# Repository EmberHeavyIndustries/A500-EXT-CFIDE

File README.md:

**A500-EXT-CFIDE** is an external IDE + Fast Memory Expansion for Amiga 500. 

It is basically a modified clone of Matthias Heinrich's CDTV-RAM-IDE board, targeted to be a quick & dirt solution for external A500/A1000 bootable mass storage (with the bonus of a RAM expansion if fitted).

The firmware is a customized version of original Matthias code, and comes thank to the wonderful kindness of Matthias himself, who put the effort and coded this derivative one as well. Thanks Matthias ! 

Within repository full schematics, board, gerbers and firmware code can be found free for everyone.
Please note that rev.1.0 board (the current one) has not been optimized against design rules, so though the project has been tested and proved fully working, a further rev.1.1 board will be released in next future, addressing all desgin "misbehaviours".

**License**

**A500-EXT-CFIDE** is Open Hardware. If you make any modifications to the board, please contribute them back.
Any derivative work must quote both the original author (Matthias Heinrich aka Matze) and EmberHeavyIndustries.

**Disclaimer**

**A500-EXT-CFIDE** is provided to you 'as is' and without any express or implied warranties whatsoever with respect to its functionality, operability or use, including, without limitation, any implied warranties of merchantability, fitness for a particular purpose or infringement. We expressly disclaim any liability whatsoever for any direct, indirect, consequential, incidental or special damages, including, without limitation, lost revenues, lost profits, losses resulting from business interruption or loss of data, regardless of the form of action or legal theory under which the liability may be asserted, even if advised of the possibility or likelihood of such damages.

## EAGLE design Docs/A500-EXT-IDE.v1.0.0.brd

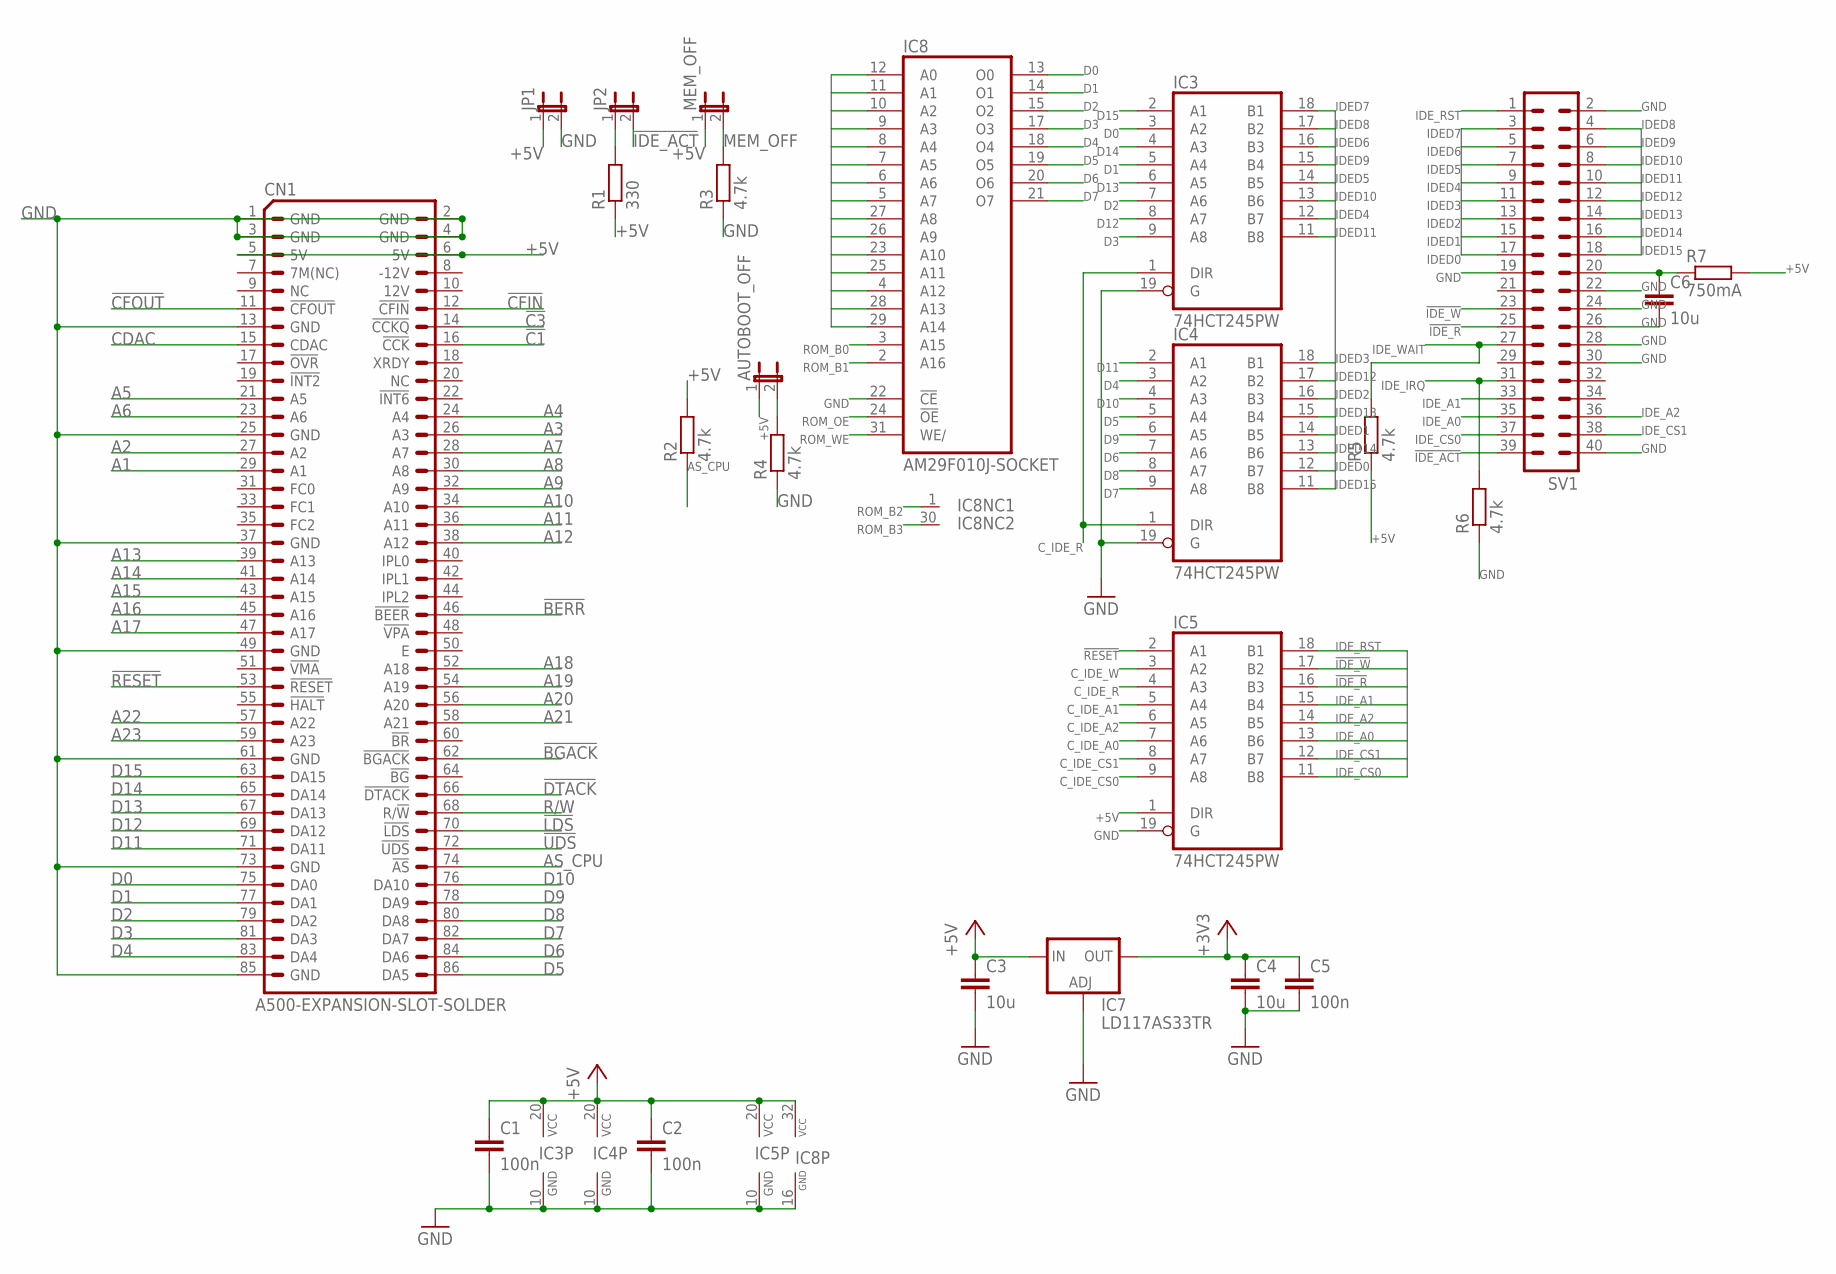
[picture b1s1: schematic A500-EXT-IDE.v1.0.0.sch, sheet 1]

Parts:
AUTOBOOT_OFF: JP1E; JP1
C1, C2, C5: 100n; C0603K
C3, C4, C6: 10u; C0805K
CN1: A500-EXPANSION-SLOT-SOLDER; LKONT_43-SLOT-SOLDER
IC3, IC4, IC5: 74HCT245PW; TSSOP20
IC7: LD117AS33TR; SOT223
IC8: AM29F010J-SOCKET; PLCC-32-SMT-TT
JP1, JP2: JP1E; JP1
MEM_OFF: JP1E; JP1
R1: 330; R0603
R2, R3, R4, R5, R6: 4.7k; R0603
R7: 750mA; R2512
SV1: ML40

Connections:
!BERR: CN1.46 (!BEER!); also elsewhere on the board
!BGACK: CN1.62 (!BGACK!); also elsewhere on the board
!C1: CN1.16 (!CCK!); also elsewhere on the board
!C3: CN1.14 (!CCKQ!); also elsewhere on the board
!CFIN: CN1.12 (!CFIN!); also elsewhere on the board
!CFOUT: CN1.11 (!CFOUT!); also elsewhere on the board
!DTACK: CN1.66 (!DTACK!); also elsewhere on the board
!IDE_ACT: JP2.2, SV1.39
!IDE_R: IC5.16 (B3), SV1.25
!IDE_W: IC5.17 (B2), SV1.23
!LDS: CN1.70 (!LDS!); also elsewhere on the board
!RESET: CN1.53 (!RESET!), IC5.2 (A1); also elsewhere on the board
!UDS: CN1.72 (!UDS!); also elsewhere on the board
+3V3: C4.1, C5.1, IC7.2 (OUT), IC7.4 (OUT); also elsewhere on the board
+5V: AUTOBOOT_OFF.1, C1.1, C2.1, C3.1, CN1.5 (5V), CN1.6 (5V), IC3.20 (VCC), IC4.20 (VCC), IC5.1 (DIR), IC5.20 (VCC), IC7.3 (IN), IC8.32 (VCC), JP1.1, MEM_OFF.1, R1.1, R2.2, R5.1, R7.2; also elsewhere on the board
A1: CN1.29 (A1), IC8.12 (A0); also elsewhere on the board
A2: CN1.27 (A2), IC8.11 (A1); also elsewhere on the board
A3: CN1.26 (A3), IC8.10 (A2); also elsewhere on the board
A4: CN1.24 (A4), IC8.9 (A3); also elsewhere on the board
A5: CN1.21 (A5), IC8.8 (A4); also elsewhere on the board
A6: CN1.23 (A6), IC8.7 (A5); also elsewhere on the board
A7: CN1.28 (A7), IC8.6 (A6); also elsewhere on the board
A8: CN1.30 (A8), IC8.5 (A7); also elsewhere on the board
A9: CN1.32 (A9), IC8.27 (A8); also elsewhere on the board
A10: CN1.34 (A10), IC8.26 (A9); also elsewhere on the board
A11: CN1.36 (A11), IC8.23 (A10); also elsewhere on the board
A12: CN1.38 (A12), IC8.25 (A11); also elsewhere on the board
A13: CN1.39 (A13), IC8.4 (A12); also elsewhere on the board
A14: CN1.41 (A14), IC8.28 (A13); also elsewhere on the board
A15: CN1.43 (A15), IC8.29 (A14); also elsewhere on the board
A16: CN1.45 (A16); also elsewhere on the board
A17: CN1.47 (A17); also elsewhere on the board
A18: CN1.52 (A18); also elsewhere on the board
A19: CN1.54 (A19); also elsewhere on the board
A20: CN1.56 (A20); also elsewhere on the board
A21: CN1.58 (A21); also elsewhere on the board
A22: CN1.57 (A22); also elsewhere on the board
A23: CN1.59 (A23); also elsewhere on the board
AS_CPU: CN1.74 (!AS!), R2.1; also elsewhere on the board
AUTO_BOOT_OFF: AUTOBOOT_OFF.2, R4.2; also elsewhere on the board
CDAC: CN1.15 (CDAC); also elsewhere on the board
C_IDE_A0: IC5.7 (A6); also elsewhere on the board
C_IDE_A1: IC5.5 (A4); also elsewhere on the board
C_IDE_A2: IC5.6 (A5); also elsewhere on the board
C_IDE_CS0: IC5.9 (A8); also elsewhere on the board
C_IDE_CS1: IC5.8 (A7); also elsewhere on the board
C_IDE_R: IC3.1 (DIR), IC4.1 (DIR), IC5.4 (A3); also elsewhere on the board
C_IDE_W: IC5.3 (A2); also elsewhere on the board
D0: CN1.75 (DA0), IC3.3 (A2), IC8.13 (O0); also elsewhere on the board
D1: CN1.77 (DA1), IC3.5 (A4), IC8.14 (O1); also elsewhere on the board
D2: CN1.79 (DA2), IC3.7 (A6), IC8.15 (O2); also elsewhere on the board
D3: CN1.81 (DA3), IC3.9 (A8), IC8.17 (O3); also elsewhere on the board
D4: CN1.83 (DA4), IC4.3 (A2), IC8.18 (O4); also elsewhere on the board
D5: CN1.86 (DA5), IC4.5 (A4), IC8.19 (O5); also elsewhere on the board
D6: CN1.84 (DA6), IC4.7 (A6), IC8.20 (O6); also elsewhere on the board
D7: CN1.82 (DA7), IC4.9 (A8), IC8.21 (O7); also elsewhere on the board
D8: CN1.80 (DA8), IC4.8 (A7); also elsewhere on the board
D9: CN1.78 (DA9), IC4.6 (A5); also elsewhere on the board
D10: CN1.76 (DA10), IC4.4 (A3); also elsewhere on the board
D11: CN1.71 (DA11), IC4.2 (A1); also elsewhere on the board
D12: CN1.69 (DA12), IC3.8 (A7); also elsewhere on the board
D13: CN1.67 (DA13), IC3.6 (A5); also elsewhere on the board
D14: CN1.65 (DA14), IC3.4 (A3); also elsewhere on the board
D15: CN1.63 (DA15), IC3.2 (A1); also elsewhere on the board
GND: C1.2, C2.2, C3.2, C4.2, C5.2, C6.2, CN1.1 (GND), CN1.2 (GND), CN1.3 (GND), CN1.4 (GND), CN1.13 (GND), CN1.25 (GND), CN1.37 (GND), CN1.49 (GND), CN1.61 (GND), CN1.73 (GND), CN1.85 (GND), IC3.10 (GND), IC3.19 (G), IC4.10 (GND), IC4.19 (G), IC5.10 (GND), IC5.19 (G), IC7.1 (ADJ), IC8.16 (GND), IC8.22 (!CE), JP1.2, R3.1, R4.1, R6.1, SV1.2, SV1.19, SV1.22, SV1.24, SV1.26, SV1.28, SV1.30, SV1.40; also elsewhere on the board
IDED0: IC4.12 (B7), SV1.17
IDED1: IC4.14 (B5), SV1.15
IDED2: IC4.16 (B3), SV1.13
IDED3: IC4.18 (B1), SV1.11
IDED4: IC3.12 (B7), SV1.9
IDED5: IC3.14 (B5), SV1.7
IDED6: IC3.16 (B3), SV1.5
IDED7: IC3.18 (B1), SV1.3
IDED8: IC3.17 (B2), SV1.4
IDED9: IC3.15 (B4), SV1.6
IDED10: IC3.13 (B6), SV1.8
IDED11: IC3.11 (B8), SV1.10
IDED12: IC4.17 (B2), SV1.12
IDED13: IC4.15 (B4), SV1.14
IDED14: IC4.13 (B6), SV1.16
IDED15: IC4.11 (B8), SV1.18
IDE_A0: IC5.13 (B6), SV1.35
IDE_A1: IC5.15 (B4), SV1.33
IDE_A2: IC5.14 (B5), SV1.36
IDE_CS0: IC5.11 (B8), SV1.37
IDE_CS1: IC5.12 (B7), SV1.38
IDE_IRQ: R6.2, SV1.31; also elsewhere on the board
IDE_RST: IC5.18 (B1), SV1.1
IDE_WAIT: R5.2, SV1.27; also elsewhere on the board
KEY_PIN_POWER: C6.1, R7.1, SV1.20
MEM_OFF: MEM_OFF.2, R3.2; also elsewhere on the board
unnamed: JP2.1, R1.2
R/W: CN1.68 (R/!W!); also elsewhere on the board
ROM_B0: IC8.3 (A15); also elsewhere on the board
ROM_B1: IC8.2 (A16); also elsewhere on the board
ROM_B2: IC8.1 (NC); also elsewhere on the board
ROM_B3: IC8.30 (NC); also elsewhere on the board
ROM_OE: IC8.24 (!OE); also elsewhere on the board
ROM_WE: IC8.31 (WE/); also elsewhere on the board

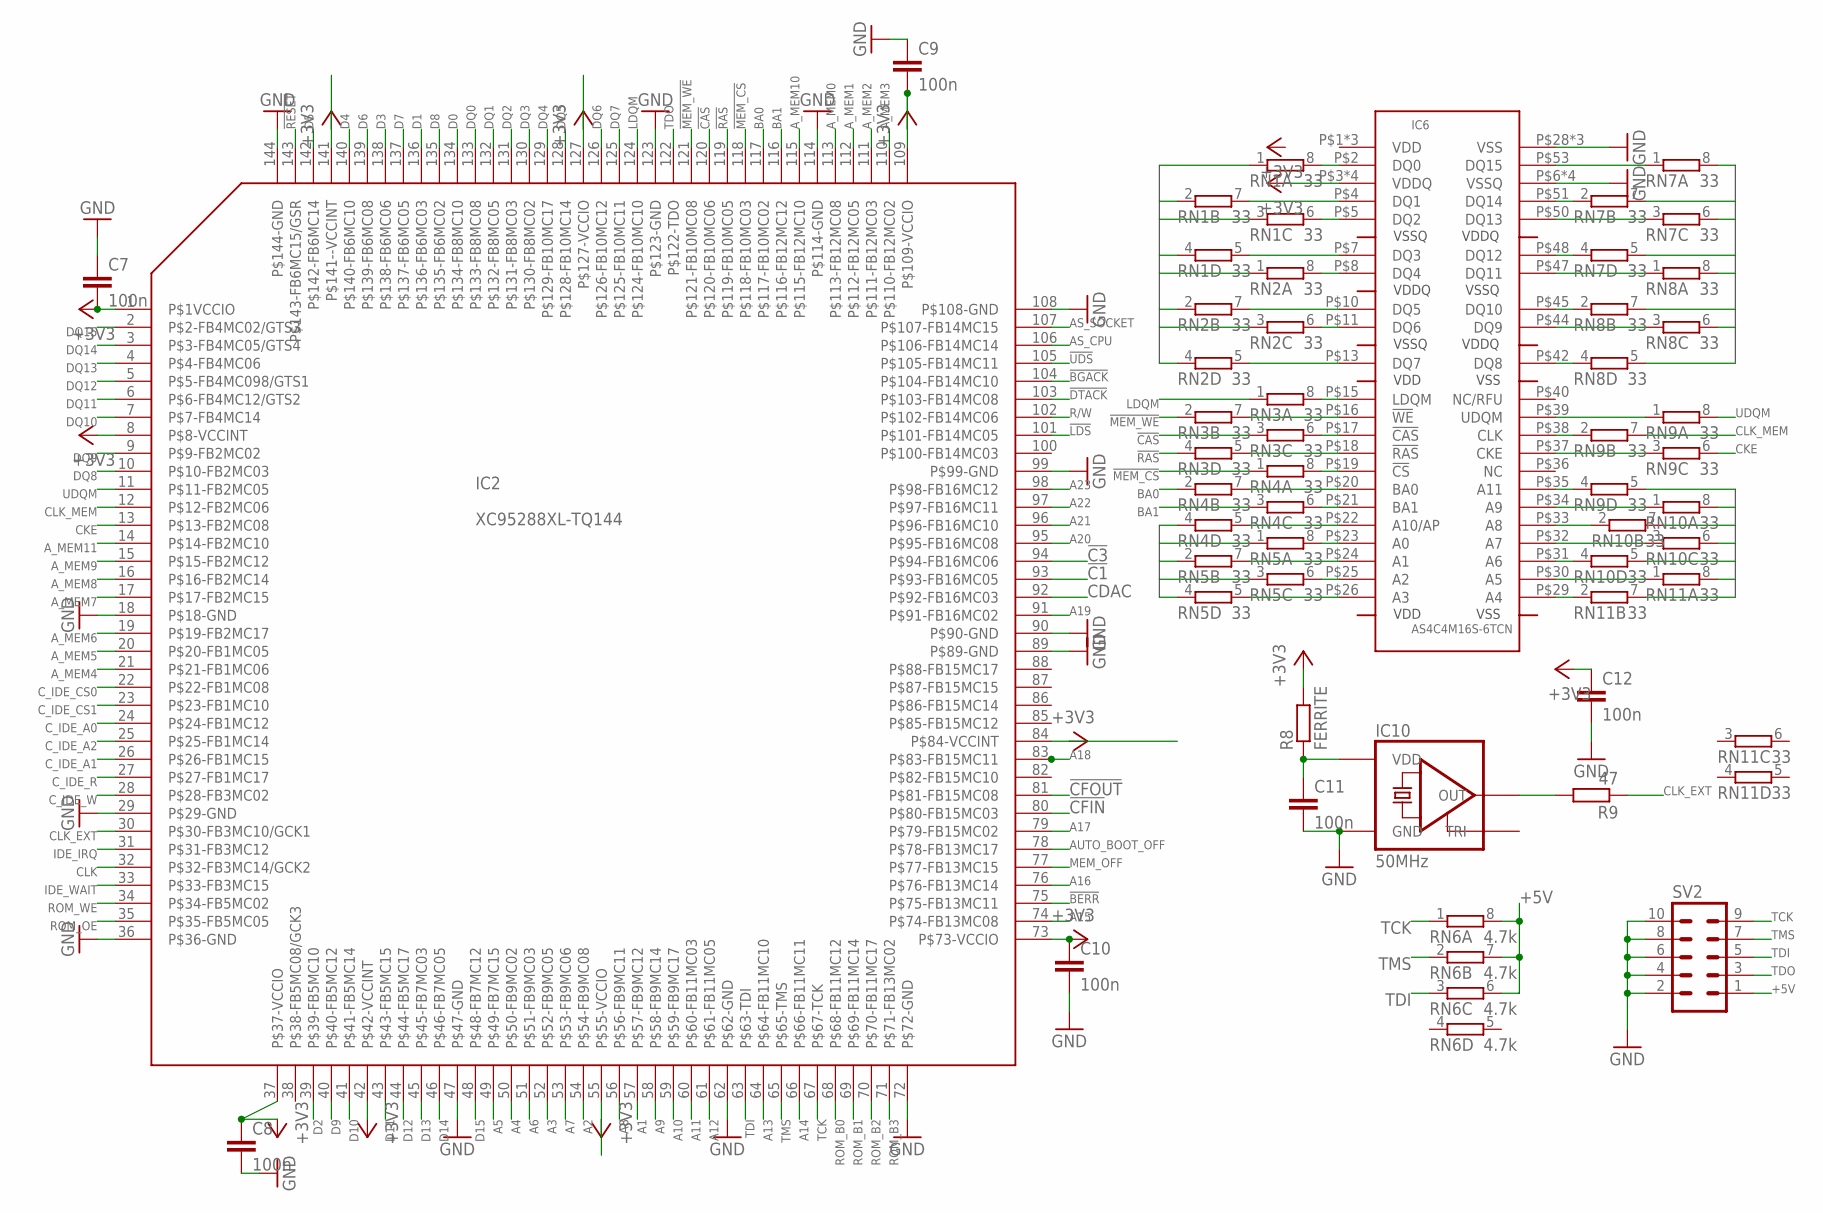
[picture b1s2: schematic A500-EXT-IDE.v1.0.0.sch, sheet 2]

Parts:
C7, C8, C9, C10, C11, C12: 100n; C0603K
IC2: XC95288XL-TQ144; TQFP144
IC6: AS4C4M16S-6TCN; TSOP-2_54
IC10: 50MHz; 7X5
R8: FERRITE; R0603
R9: 47; R0603
RN1, RN2, RN3, RN4, RN5, RN7, RN8, RN9, RN10, RN11: 33; CAY16
RN6: 4.7k; CAY16
SV2: ML10L

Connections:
!BERR: IC2.75 (P$75-FB13MC11); also elsewhere on the board
!BGACK: IC2.104 (P$104-FB14MC10); also elsewhere on the board
!C1: IC2.93 (P$93-FB16MC05); also elsewhere on the board
!C3: IC2.94 (P$94-FB16MC06); also elsewhere on the board
!CAS: IC2.120 (P$120-FB10MC06), RN3.3 (1)
!CFIN: IC2.80 (P$80-FB15MC03); also elsewhere on the board
!CFOUT: IC2.81 (P$81-FB15MC08); also elsewhere on the board
!DTACK: IC2.103 (P$103-FB14MC08); also elsewhere on the board
!LDS: IC2.101 (P$101-FB14MC05); also elsewhere on the board
!MEM_CS: IC2.118 (P$118-FB10MC03), RN4.1
!MEM_WE: IC2.121 (P$121-FB10MC08), RN3.2 (1)
!RAS: IC2.119 (P$119-FB10MC05), RN3.4 (1)
!RESET: IC2.143 (P$143-FB6MC15/GSR); also elsewhere on the board
!UDS: IC2.105 (P$105-FB14MC11); also elsewhere on the board
+3V3: C7.2, C8.1, C9.2, C10.1, C12.1, IC2.1 (P$1VCCIO), IC2.8 (P$8-VCCINT), IC2.37 (P$37-VCCIO), IC2.42 (P$42-VCCINT), IC2.55 (P$55-VCCIO), IC2.73 (P$73-VCCIO), IC2.84 (P$84-VCCINT), IC2.109 (P$109-VCCIO), IC2.127 (P$127-VCCIO), IC2.141 (P$141--VCCINT), IC6.P$3 (VDDQ), IC6.P$9 (VDDQ), IC6.P$43 (VDDQ), IC6.P$49 (VDDQ), R8.2; also elsewhere on the board
+5V: RN6.6 (2), RN6.7 (2), RN6.8 (2), SV2.1; also elsewhere on the board
A1: IC2.57 (P$57-FB9MC12); also elsewhere on the board
A2: IC2.54 (P$54-FB9MC08); also elsewhere on the board
A3: IC2.52 (P$52-FB9MC05); also elsewhere on the board
A4: IC2.50 (P$50-FB9MC02); also elsewhere on the board
A5: IC2.49 (P$49-FB7MC15); also elsewhere on the board
A6: IC2.51 (P$51-FB9MC03); also elsewhere on the board
A7: IC2.53 (P$53-FB9MC06); also elsewhere on the board
A8: IC2.56 (P$56-FB9MC11); also elsewhere on the board
A9: IC2.58 (P$58-FB9MC14); also elsewhere on the board
A10: IC2.59 (P$59-FB9MC17); also elsewhere on the board
A11: IC2.60 (P$60-FB11MC03); also elsewhere on the board
A12: IC2.61 (P$61-FB11MC05); also elsewhere on the board
A13: IC2.64 (P$64-FB11MC10); also elsewhere on the board
A14: IC2.66 (P$66-FB11MC11); also elsewhere on the board
A15: IC2.74 (P$74-FB13MC08); also elsewhere on the board
A16: IC2.76 (P$76-FB13MC14); also elsewhere on the board
A17: IC2.79 (P$79-FB15MC02); also elsewhere on the board
A18: IC2.83 (P$83-FB15MC11); also elsewhere on the board
A19: IC2.91 (P$91-FB16MC02); also elsewhere on the board
A20: IC2.95 (P$95-FB16MC08); also elsewhere on the board
A21: IC2.96 (P$96-FB16MC10); also elsewhere on the board
A22: IC2.97 (P$97-FB16MC11); also elsewhere on the board
A23: IC2.98 (P$98-FB16MC12); also elsewhere on the board
AS_CPU: IC2.106 (P$106-FB14MC14); also elsewhere on the board
AS_SOCKET: IC2.107 (P$107-FB14MC15)
AUTO_BOOT_OFF: IC2.78 (P$78-FB13MC17); also elsewhere on the board
A_MEM0: IC2.113 (P$113-FB12MC08), RN5.1
A_MEM1: IC2.112 (P$112-FB12MC05), RN5.2 (1)
A_MEM2: IC2.111 (P$111-FB12MC03), RN5.3 (1)
A_MEM3: IC2.110 (P$110-FB12MC02), RN5.4 (1)
A_MEM4: IC2.21 (P$21-FB1MC06), RN11.7 (2)
A_MEM5: IC2.20 (P$20-FB1MC05), RN11.8 (2)
A_MEM6: IC2.19 (P$19-FB2MC17), RN10.5 (2)
A_MEM7: IC2.17 (P$17-FB2MC15), RN10.6 (2)
A_MEM8: IC2.16 (P$16-FB2MC14), RN10.7 (2)
A_MEM9: IC2.15 (P$15-FB2MC12), RN10.8 (2)
A_MEM10: IC2.115 (P$115-FB12MC10), RN4.4 (1)
A_MEM11: IC2.14 (P$14-FB2MC10), RN9.5 (2)
BA0: IC2.117 (P$117-FB10MC02), RN4.2 (1)
BA1: IC2.116 (P$116-FB12MC12), RN4.3 (1)
CDAC: IC2.92 (P$92-FB16MC03); also elsewhere on the board
CKE: IC2.13 (P$13-FB2MC08), RN9.6 (2)
CLK: IC2.32 (P$32-FB3MC14/GCK2)
CLK_EXT: IC2.30 (P$30-FB3MC10/GCK1), R9.1
CLK_MEM: IC2.12 (P$12-FB2MC06), RN9.7 (2)
C_IDE_A0: IC2.24 (P$24-FB1MC12); also elsewhere on the board
C_IDE_A1: IC2.26 (P$26-FB1MC15); also elsewhere on the board
C_IDE_A2: IC2.25 (P$25-FB1MC14); also elsewhere on the board
C_IDE_CS0: IC2.22 (P$22-FB1MC08); also elsewhere on the board
C_IDE_CS1: IC2.23 (P$23-FB1MC10); also elsewhere on the board
C_IDE_R: IC2.27 (P$27-FB1MC17); also elsewhere on the board
C_IDE_W: IC2.28 (P$28-FB3MC02); also elsewhere on the board
D0: IC2.134 (P$134-FB8MC10); also elsewhere on the board
D1: IC2.136 (P$136-FB6MC03); also elsewhere on the board
D2: IC2.39 (P$39-FB5MC10); also elsewhere on the board
D3: IC2.138 (P$138-FB6MC06); also elsewhere on the board
D4: IC2.140 (P$140-FB6MC10); also elsewhere on the board
D5: IC2.142 (P$142-FB6MC14); also elsewhere on the board
D6: IC2.139 (P$139-FB6MC08); also elsewhere on the board
D7: IC2.137 (P$137-FB6MC05); also elsewhere on the board
D8: IC2.135 (P$135-FB6MC02); also elsewhere on the board
D9: IC2.40 (P$40-FB5MC12); also elsewhere on the board
D10: IC2.41 (P$41-FB5MC14); also elsewhere on the board
D11: IC2.43 (P$43-FB5MC15); also elsewhere on the board
D12: IC2.44 (P$44-FB5MC17); also elsewhere on the board
D13: IC2.45 (P$45-FB7MC03); also elsewhere on the board
D14: IC2.46 (P$46-FB7MC05); also elsewhere on the board
D15: IC2.48 (P$48-FB7MC12); also elsewhere on the board
DQ0: IC2.133 (P$133-FB8MC08), RN1.1
DQ1: IC2.132 (P$132-FB8MC05), RN1.2 (1)
DQ2: IC2.131 (P$131-FB8MC03), RN1.3 (1)
DQ3: IC2.130 (P$130-FB8MC02), RN1.4 (1)
DQ4: IC2.129 (P$129-FB10MC17), RN2.1
DQ5: IC2.128 (P$128-FB10MC14), RN2.2 (1)
DQ6: IC2.126 (P$126-FB10MC12), RN2.3 (1)
DQ7: IC2.125 (P$125-FB10MC11), RN2.4 (1)
DQ8: IC2.10 (P$10-FB2MC03), RN8.5 (2)
DQ9: IC2.9 (P$9-FB2MC02), RN8.6 (2)
DQ10: IC2.7 (P$7-FB4MC14), RN8.7 (2)
DQ11: IC2.6 (P$6-FB4MC12/GTS2), RN8.8 (2)
DQ12: IC2.5 (P$5-FB4MC098/GTS1), RN7.5 (2)
DQ13: IC2.4 (P$4-FB4MC06), RN7.6 (2)
DQ14: IC2.3 (P$3-FB4MC05/GTS4), RN7.7 (2)
DQ15: IC2.2 (P$2-FB4MC02/GTS3), RN7.8 (2)
GND: C7.1, C8.2, C9.1, C10.2, C11.2, C12.2, IC2.18 (P$18-GND), IC2.29 (P$29-GND), IC2.36 (P$36-GND), IC2.47 (P$47-GND), IC2.62 (P$62-GND), IC2.72 (P$72-GND), IC2.89 (P$89-GND), IC2.90 (P$90-GND), IC2.99 (P$99-GND), IC2.108 (P$108-GND), IC2.114 (P$114-GND), IC2.123 (P$123-GND), IC2.144 (P$144-GND), IC6.P$6 (VSSQ), IC6.P$12 (VSSQ), IC6.P$28 (VSS), IC6.P$41 (VSS), IC6.P$46 (VSSQ), IC6.P$52 (VSSQ), IC6.P$54 (VSS), IC10.P$2 (GND), SV2.2, SV2.4, SV2.6, SV2.8, SV2.10; also elsewhere on the board
IDE_IRQ: IC2.31 (P$31-FB3MC12); also elsewhere on the board
IDE_WAIT: IC2.33 (P$33-FB3MC15); also elsewhere on the board
LDQM: IC2.124 (P$124-FB10MC10), RN3.1
MEM_OFF: IC2.77 (P$77-FB13MC15); also elsewhere on the board
unnamed: IC6.P$26 (A3), RN5.5 (2)
unnamed: IC6.P$25 (A2), RN5.6 (2)
unnamed: IC6.P$24 (A1), RN5.7 (2)
unnamed: IC6.P$23 (A0), RN5.8 (2)
unnamed: IC6.P$22 (A10/AP), RN4.5 (2)
unnamed: IC6.P$21 (BA1), RN4.6 (2)
unnamed: IC6.P$20 (BA0), RN4.7 (2)
unnamed: IC6.P$19 (!CS), RN4.8 (2)
unnamed: IC6.P$18 (!RAS), RN3.5 (2)
unnamed: IC6.P$17 (!CAS), RN3.6 (2)
unnamed: IC6.P$16 (!WE), RN3.7 (2)
unnamed: IC6.P$15 (LDQM), RN3.8 (2)
unnamed: IC6.P$13 (DQ7), RN2.5 (2)
unnamed: IC6.P$11 (DQ6), RN2.6 (2)
unnamed: IC6.P$10 (DQ5), RN2.7 (2)
unnamed: IC6.P$8 (DQ4), RN2.8 (2)
unnamed: IC6.P$7 (DQ3), RN1.5 (2)
unnamed: IC6.P$5 (DQ2), RN1.6 (2)
unnamed: IC6.P$4 (DQ1), RN1.7 (2)
unnamed: IC6.P$2 (DQ0), RN1.8 (2)
unnamed: IC6.P$53 (DQ15), RN7.1
unnamed: IC6.P$51 (DQ14), RN7.2 (1)
unnamed: IC6.P$50 (DQ13), RN7.3 (1)
unnamed: IC6.P$48 (DQ12), RN7.4 (1)
unnamed: IC6.P$47 (DQ11), RN8.1
unnamed: IC6.P$45 (DQ10), RN8.2 (1)
unnamed: IC6.P$44 (DQ9), RN8.3 (1)
unnamed: IC6.P$42 (DQ8), RN8.4 (1)
unnamed: IC6.P$39 (UDQM), RN9.1
unnamed: IC6.P$38 (CLK), RN9.2 (1)
unnamed: IC6.P$37 (CKE), RN9.3 (1)
unnamed: IC6.P$35 (A11), RN9.4 (1)
unnamed: IC6.P$34 (A9), RN10.1
unnamed: IC6.P$33 (A8), RN10.2 (1)
unnamed: IC6.P$32 (A7), RN10.3 (1)
unnamed: IC6.P$31 (A6), RN10.4 (1)
unnamed: IC6.P$30 (A5), RN11.1
unnamed: IC6.P$29 (A4), RN11.2 (1)
unnamed: IC10.P$3 (OUT), R9.2
R/W: IC2.102 (P$102-FB14MC06); also elsewhere on the board
ROM_B0: IC2.68 (P$68-FB11MC12); also elsewhere on the board
ROM_B1: IC2.69 (P$69-FB11MC14); also elsewhere on the board
ROM_B2: IC2.70 (P$70-FB11MC17); also elsewhere on the board
ROM_B3: IC2.71 (P$71-FB13MC02); also elsewhere on the board
ROM_OE: IC2.35 (P$35-FB5MC05); also elsewhere on the board
ROM_WE: IC2.34 (P$34-FB5MC02); also elsewhere on the board
TCK: IC2.67 (P$67-TCK), RN6.1, SV2.9
TDI: IC2.63 (P$63-TDI), RN6.3 (1), SV2.5
TDO: IC2.122 (P$122-TDO), SV2.3
TMS: IC2.65 (P$65-TMS), RN6.2 (1), SV2.7
UDQM: IC2.11 (P$11-FB2MC05), RN9.8 (2)
VCC-X: C11.1, IC10.P$4 (VDD), R8.1

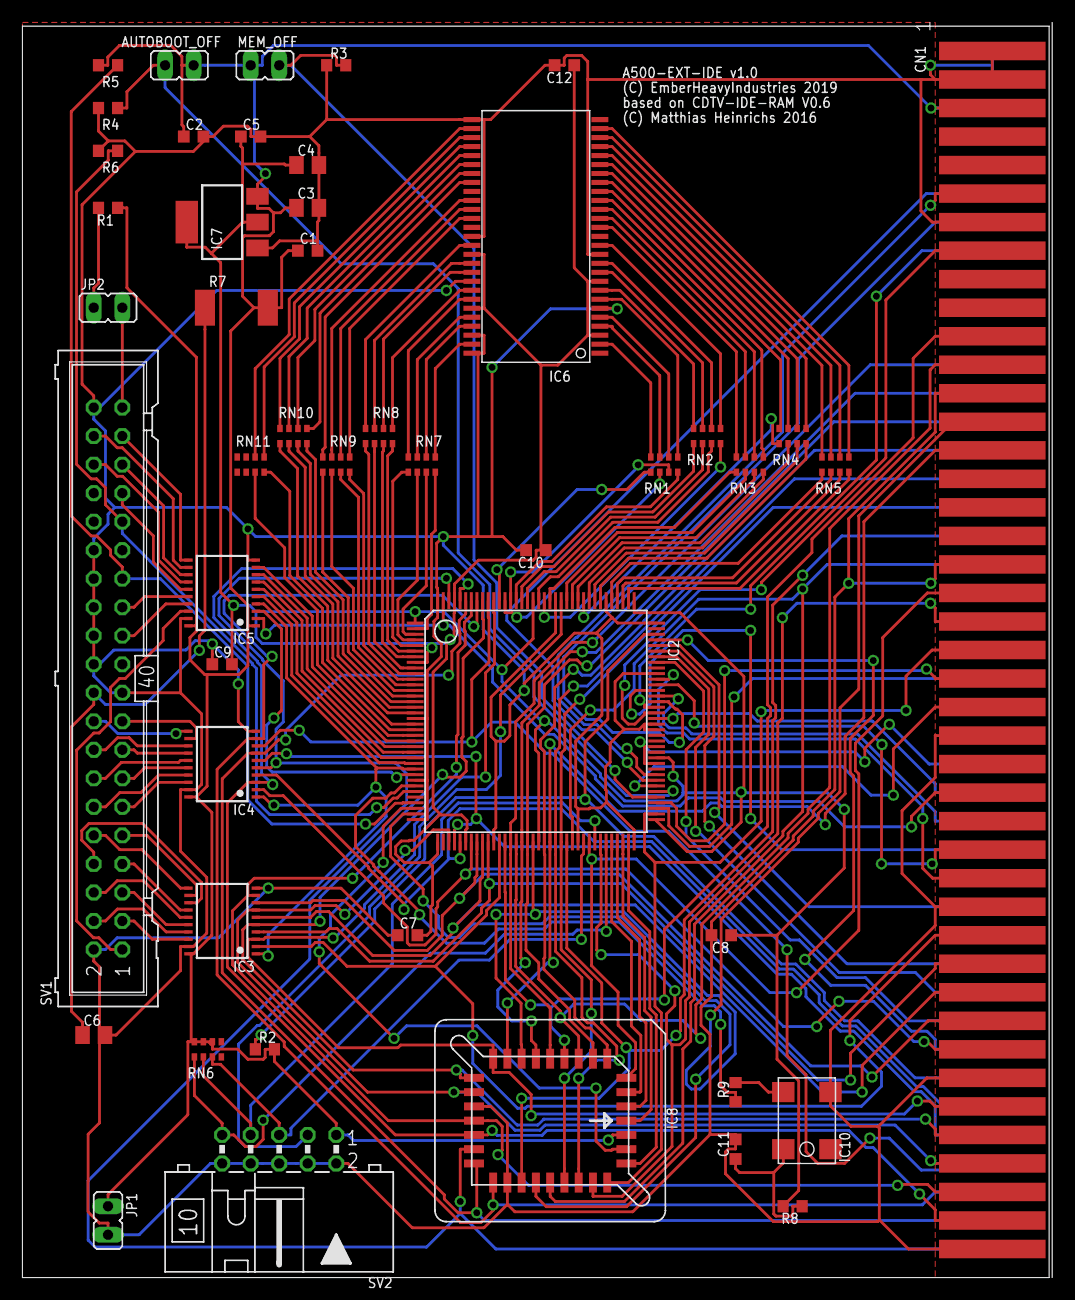
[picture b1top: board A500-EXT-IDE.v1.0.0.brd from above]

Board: 2 copper layers, 91.4 x 111.4 mm, 47 parts (0 on the bottom side), 182 nets.

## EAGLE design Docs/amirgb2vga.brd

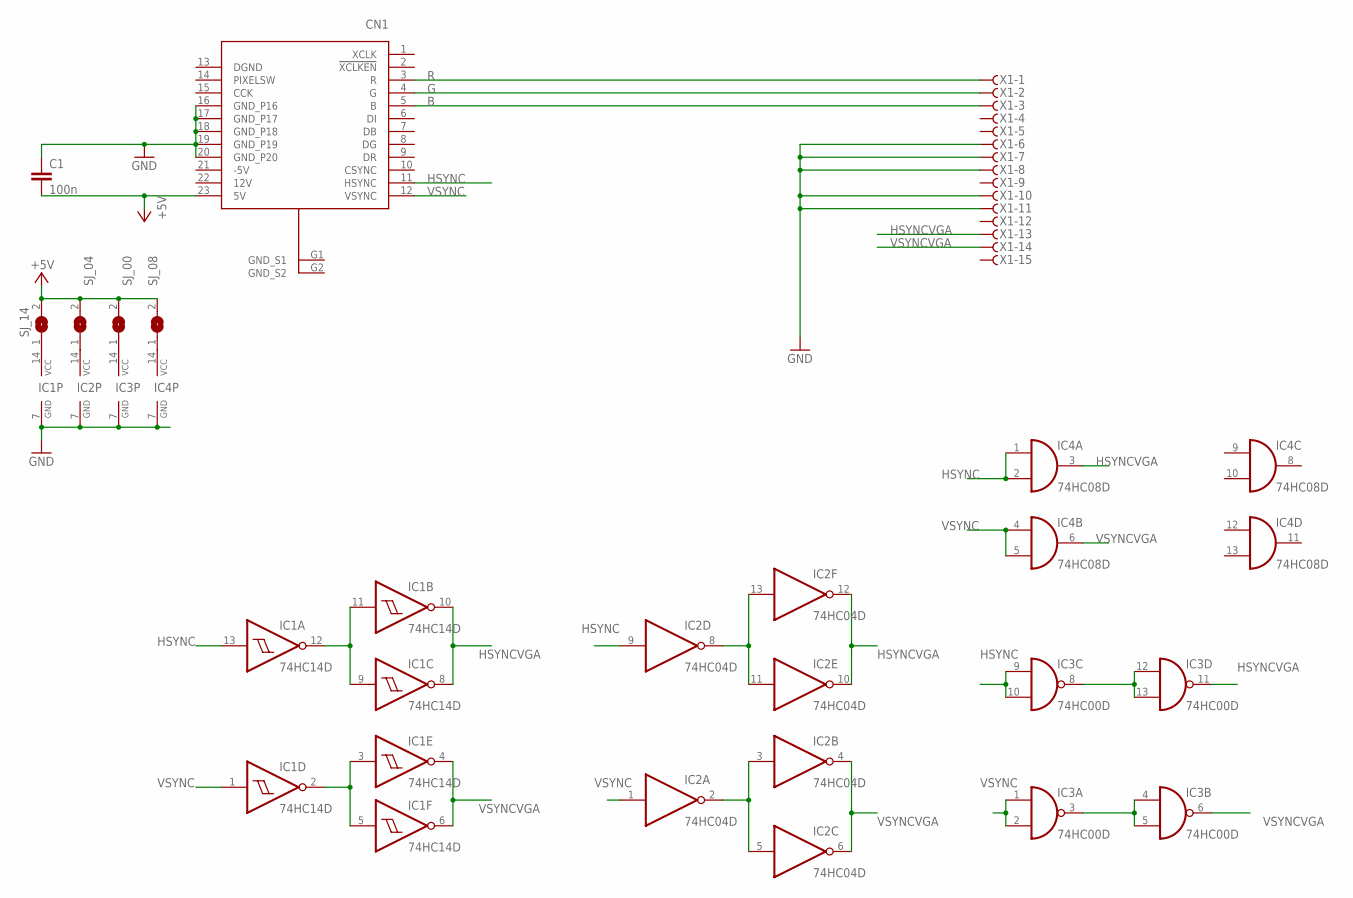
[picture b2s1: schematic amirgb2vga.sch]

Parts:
C1: 100n; C0805
CN1: VIDEO_PORT_MALE_23D_SUB_F; F23H_FC
IC1: 74HC14D; SO14
IC2: 74HC04D; SO14
IC3: 74HC00D; SO14
IC4: 74HC08D; SO14
SJ_00, SJ_04, SJ_08, SJ_14: SJ
X1: HF15HS; HDF15H

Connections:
+5V: C1.2, CN1.23 (5V), SJ_00.2, SJ_04.2, SJ_08.2, SJ_14.2
B: CN1.5 (B), X1.3
G: CN1.4 (G), X1.2
GND: C1.1, CN1.16 (GND_P16), CN1.17 (GND_P17), CN1.18 (GND_P18), CN1.19 (GND_P19), CN1.20 (GND_P20), IC1.7 (GND), IC2.7 (GND), IC3.7 (GND), IC4.7 (GND), X1.6, X1.7, X1.8, X1.10, X1.11
GND_S1: CN1.G1 (GND_S1)
GND_S2: CN1.G2 (GND_S2)
HSYNC: CN1.11 (HSYNC), IC1.13 (I), IC2.9 (I), IC3.9 (I0), IC3.10 (I1), IC4.1 (I0), IC4.2 (I1)
HSYNCVGA: IC1.8 (O), IC1.10 (O), IC2.10 (O), IC2.12 (O), IC3.11 (O), IC4.3 (O), X1.13
unnamed: IC1.14 (VCC), SJ_14.1
unnamed: IC1.2 (O), IC1.3 (I), IC1.5 (I)
unnamed: IC4.14 (VCC), SJ_08.1
unnamed: IC2.14 (VCC), SJ_04.1
unnamed: IC1.9 (I), IC1.11 (I), IC1.12 (O)
unnamed: IC3.14 (VCC), SJ_00.1
unnamed: IC2.8 (O), IC2.11 (I), IC2.13 (I)
unnamed: IC2.2 (O), IC2.3 (I), IC2.5 (I)
unnamed: IC3.8 (O), IC3.12 (I0), IC3.13 (I1)
unnamed: IC3.3 (O), IC3.4 (I0), IC3.5 (I1)
R: CN1.3 (R), X1.1
VSYNC: CN1.12 (VSYNC), IC1.1 (I), IC2.1 (I), IC3.1 (I0), IC3.2 (I1), IC4.4 (I0), IC4.5 (I1)
VSYNCVGA: IC1.4 (O), IC1.6 (O), IC2.4 (O), IC2.6 (O), IC3.6 (O), IC4.6 (O), X1.14

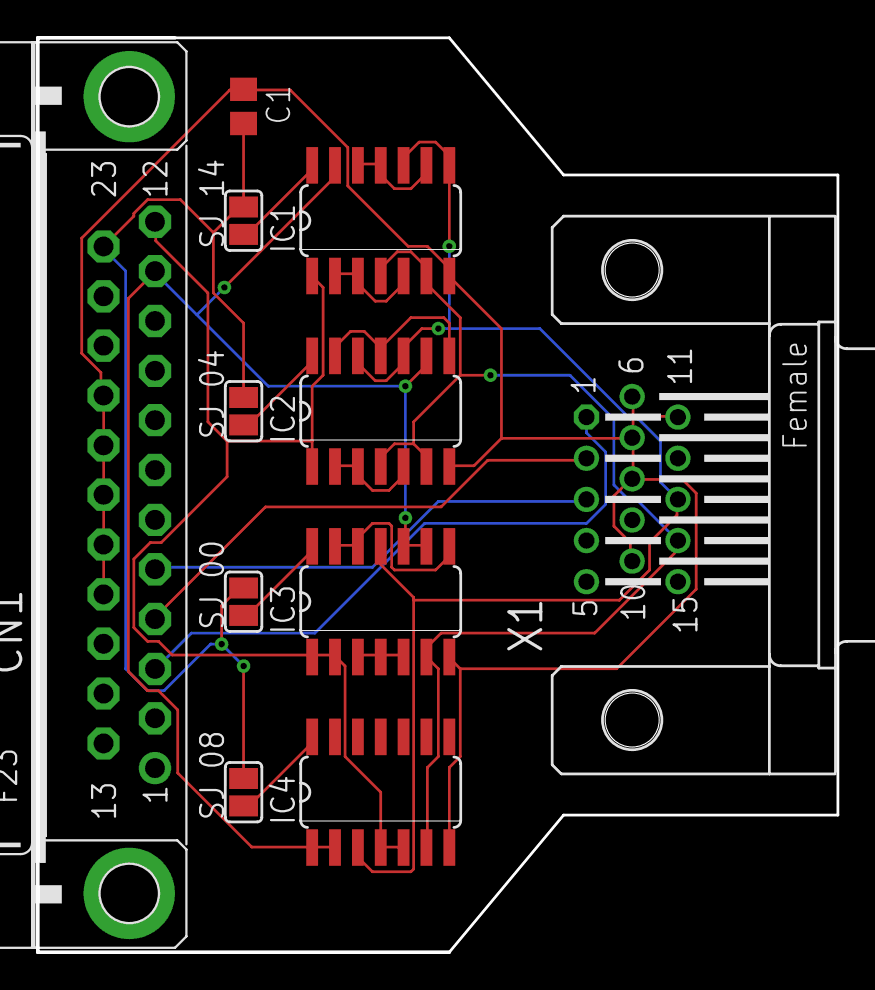
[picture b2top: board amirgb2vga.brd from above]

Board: 2 copper layers, 44.5 x 50.8 mm, 11 parts (0 on the bottom side), 19 nets.

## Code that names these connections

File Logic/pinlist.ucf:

#amiga busses
#amiga signals
#RAM signals
#IDE signals
#rom signals
#controll signals
#PACE: Start of Constraints generated by PACE

#PACE: Start of PACE I/O Pin Assignments
NET "A<1>"  LOC = "P57"  ; 
NET "A<2>"  LOC = "P54"  ; 
NET "A<3>"  LOC = "P52"  ; 
NET "A<4>"  LOC = "P50"  ; 
NET "A<5>"  LOC = "P49"  ; 
NET "A<6>"  LOC = "P51"  ; 
NET "A<7>"  LOC = "P53"  ; 
NET "A<8>"  LOC = "P56"  ; 
NET "A<9>"  LOC = "P58"  ; 
NET "A<10>"  LOC = "P59"  ; 
NET "A<11>"  LOC = "P60"  ; 
NET "A<12>"  LOC = "P61"  ; 
NET "A<13>"  LOC = "P64"  ; 
NET "A<14>"  LOC = "P66"  ; 
NET "A<15>"  LOC = "P74"  ; 
NET "A<16>"  LOC = "P76"  ; 
NET "A<17>"  LOC = "P79"  ; 
NET "A<18>"  LOC = "P83"  ; 
NET "A<19>"  LOC = "P91"  ; 
NET "A<20>"  LOC = "P95"  ; 
NET "A<21>"  LOC = "P96"  ; 
NET "A<22>"  LOC = "P97"  ; 
NET "A<23>"  LOC = "P98"  ; 
NET "C1"  LOC = "P93"  ; 
NET "C3"  LOC = "P94"  ; 
NET "CDAC"  LOC = "P92"  ; 
NET "ARAM<0>"  LOC = "P113"  ; 
NET "ARAM<1>"  LOC = "P112"  ; 
NET "ARAM<2>"  LOC = "P111"  ; 
NET "ARAM<3>"  LOC = "P110"  ; 
NET "ARAM<4>"  LOC = "P21"  ; 
NET "ARAM<5>"  LOC = "P20"  ; 
NET "ARAM<6>"  LOC = "P19"  ; 
NET "ARAM<7>"  LOC = "P17"  ; 
NET "ARAM<8>"  LOC = "P16"  ; 
NET "ARAM<9>"  LOC = "P15"  ; 
NET "ARAM<10>"  LOC = "P115"  ; 
NET "ARAM<11>"  LOC = "P14"  ; 
NET "AS"  LOC = "P106"  ; 
NET "BA<0>"  LOC = "P117"  ; 
NET "BA<1>"  LOC = "P116"  ; 
NET "BERR"  LOC = "P75"  ; 
NET "CAS"  LOC = "P120"  ; 
NET "CKE"  LOC = "P13"  ; 
NET "CLK50M"  LOC = "P30"  ; 
NET "CLK_MEM"  LOC = "P12"  ; 
NET "CF_IN"  LOC = "P80"  ; 
NET "CF_OUT"  LOC = "P81"  ; 
NET "D<0>"  LOC = "P134"  ; 
NET "D<1>"  LOC = "P136"  ; 
NET "D<2>"  LOC = "P39"  ; 
NET "D<3>"  LOC = "P138"  ; 
NET "D<4>"  LOC = "P140"  ; 
NET "D<5>"  LOC = "P142"  ; 
NET "D<6>"  LOC = "P139"  ; 
NET "D<7>"  LOC = "P137"  ; 
NET "D<8>"  LOC = "P135"  ; 
NET "D<9>"  LOC = "P40"  ; 
NET "D<10>"  LOC = "P41"  ; 
NET "D<11>"  LOC = "P43"  ; 
NET "D<12>"  LOC = "P44"  ; 
NET "D<13>"  LOC = "P45"  ; 
NET "D<14>"  LOC = "P46"  ; 
NET "D<15>"  LOC = "P48"  ; 
NET "DRAM<0>"  LOC = "P133"  ; 
NET "DRAM<1>"  LOC = "P132"  ; 
NET "DRAM<2>"  LOC = "P131"  ; 
NET "DRAM<3>"  LOC = "P130"  ; 
NET "DRAM<4>"  LOC = "P129"  ; 
NET "DRAM<5>"  LOC = "P128"  ; 
NET "DRAM<6>"  LOC = "P126"  ; 
NET "DRAM<7>"  LOC = "P125"  ; 
NET "DRAM<8>"  LOC = "P10"  ; 
NET "DRAM<9>"  LOC = "P9"  ; 
NET "DRAM<10>"  LOC = "P7"  ; 
NET "DRAM<11>"  LOC = "P6"  ; 
NET "DRAM<12>"  LOC = "P5"  ; 
NET "DRAM<13>"  LOC = "P4"  ; 
NET "DRAM<14>"  LOC = "P3"  ; 
NET "DRAM<15>"  LOC = "P2"  ; 
NET "DTACK"  LOC = "P103"  ; 
NET "IDE_A<0>"  LOC = "P24"  ; 
NET "IDE_A<1>"  LOC = "P26"  ; 
NET "IDE_A<2>"  LOC = "P25"  ; 
NET "IDE_CS<0>"  LOC = "P22"  ; 
NET "IDE_CS<1>"  LOC = "P23"  ; 
NET "IDE_IRQ"  LOC = "P31"  ; 
NET "IDE_OFF"  LOC = "P78"  ; 
NET "IDE_R"  LOC = "P27"  ; 
NET "IDE_W"  LOC = "P28"  ; 
NET "IDE_WAIT"  LOC = "P33"  ; 
NET "LDQM"  LOC = "P124"  ; 
NET "LDS"  LOC = "P101"  ; 
NET "MEM_CS"  LOC = "P118"  ; 
NET "MEM_OFF"  LOC = "P77"  ; 
NET "MEM_WE"  LOC = "P121"  ; 
NET "RAS"  LOC = "P119"  ; 
NET "RESET"  LOC = "P143"  ; 
NET "ROM_BANK<0>"  LOC = "P68"  ; 
NET "ROM_BANK<1>"  LOC = "P69"  ; 
NET "ROM_BANK<2>"  LOC = "P71"  ; 
NET "ROM_BANK<3>"  LOC = "P70"  ; 
NET "ROM_OE"  LOC = "P35"  ; 
NET "ROM_WE"  LOC = "P34"  ; 
NET "RW"  LOC = "P102"  ; 
NET "UDQM"  LOC = "P11"  ; 
NET "UDS"  LOC = "P105"  ; 

#PACE: Start of PACE Area Constraints

#PACE: Start of PACE Prohibit Constraints

#PACE: End of Constraints generated by PACE

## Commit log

2019-05-02 Create dummy
2019-08-23 Added initial Firmware for Rev 1.0

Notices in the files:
Docs/amirgb2vga.brd:
© 2019 bt EmberHeavyIndustries
